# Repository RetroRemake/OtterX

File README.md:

# OtterX

An Open Source 6502-based, Commander X16-compatible, 8-bit Computer

## Where to buy?

Looking to order and build your own OtterX? Official kits are available from:

[Wavicle's store on Lectronz](https://lectronz.com/products/otterx-8-bit-retro-computer)

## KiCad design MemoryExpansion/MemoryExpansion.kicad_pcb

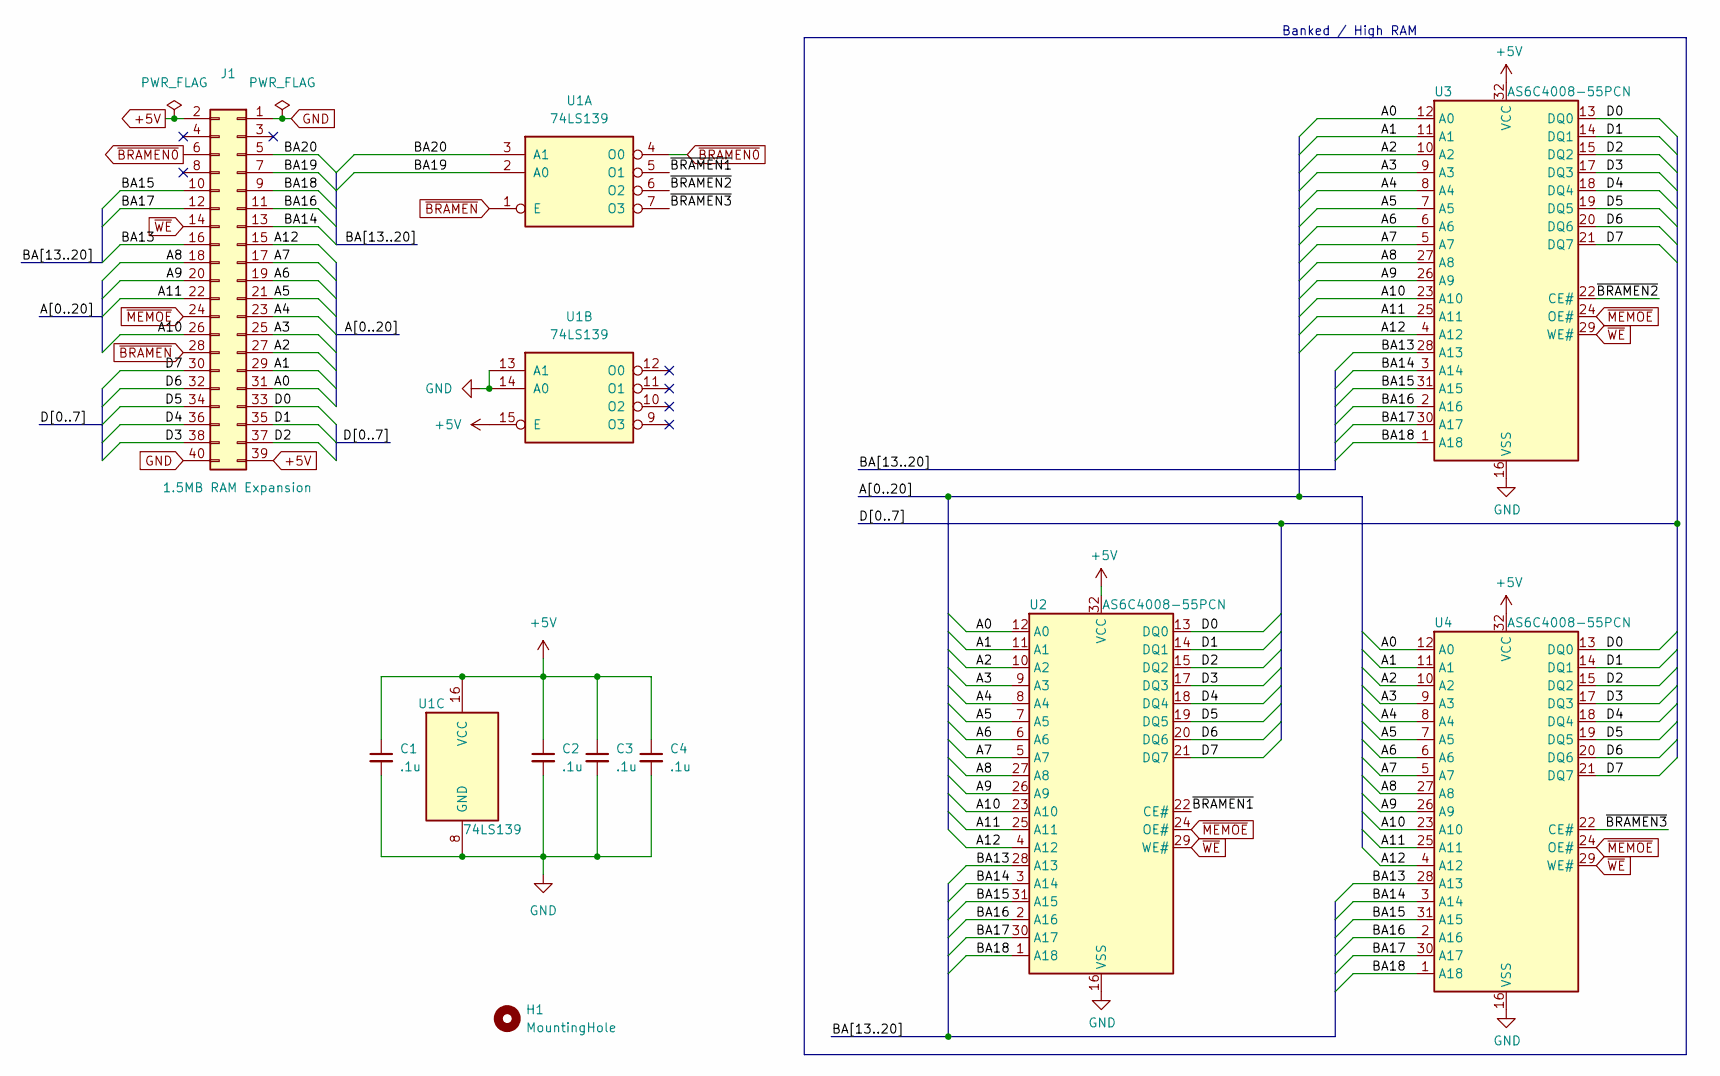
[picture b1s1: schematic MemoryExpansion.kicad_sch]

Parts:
C1, C2, C3, C4: .1u; C_Disc_D5.0mm_W2.5mm_P5.00mm
H1: MountingHole; MountingHole_2.2mm_M2
J1: 1.5MB RAM Expansion; PinHeader_2x20_P2.00mm_Vertical
U1: 74LS139; DIP-16_W7.62mm
U2, U3, U4: AS6C4008-55PCN; DIP-32_W15.24mm

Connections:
+5V: C1.1, C2.1, C3.1, C4.1, J1.2, J1.39, U1.15 (E), U1.16 (VCC), U2.32 (VCC), U3.32 (VCC), U4.32 (VCC)
/A0: J1.31, U2.12 (A0), U3.12 (A0), U4.12 (A0)
/A1: J1.29, U2.11 (A1), U3.11 (A1), U4.11 (A1)
/A2: J1.27, U2.10 (A2), U3.10 (A2), U4.10 (A2)
/A3: J1.25, U2.9 (A3), U3.9 (A3), U4.9 (A3)
/A4: J1.23, U2.8 (A4), U3.8 (A4), U4.8 (A4)
/A5: J1.21, U2.7 (A5), U3.7 (A5), U4.7 (A5)
/A6: J1.19, U2.6 (A6), U3.6 (A6), U4.6 (A6)
/A7: J1.17, U2.5 (A7), U3.5 (A7), U4.5 (A7)
/A8: J1.18, U2.27 (A8), U3.27 (A8), U4.27 (A8)
/A9: J1.20, U2.26 (A9), U3.26 (A9), U4.26 (A9)
/A10: J1.26, U2.23 (A10), U3.23 (A10), U4.23 (A10)
/A11: J1.22, U2.25 (A11), U3.25 (A11), U4.25 (A11)
/A12: J1.15, U2.4 (A12), U3.4 (A12), U4.4 (A12)
/BA13: J1.16, U2.28 (A13), U3.28 (A13), U4.28 (A13)
/BA14: J1.13, U2.3 (A14), U3.3 (A14), U4.3 (A14)
/BA15: J1.10, U2.31 (A15), U3.31 (A15), U4.31 (A15)
/BA16: J1.11, U2.2 (A16), U3.2 (A16), U4.2 (A16)
/BA17: J1.12, U2.30 (A17), U3.30 (A17), U4.30 (A17)
/BA18: J1.9, U2.1 (A18), U3.1 (A18), U4.1 (A18)
/BA19: J1.7, U1.2 (A0)
/BA20: J1.5, U1.3 (A1)
/D0: J1.33, U2.13 (DQ0), U3.13 (DQ0), U4.13 (DQ0)
/D1: J1.35, U2.14 (DQ1), U3.14 (DQ1), U4.14 (DQ1)
/D2: J1.37, U2.15 (DQ2), U3.15 (DQ2), U4.15 (DQ2)
/D3: J1.38, U2.17 (DQ3), U3.17 (DQ3), U4.17 (DQ3)
/D4: J1.36, U2.18 (DQ4), U3.18 (DQ4), U4.18 (DQ4)
/D5: J1.34, U2.19 (DQ5), U3.19 (DQ5), U4.19 (DQ5)
/D6: J1.32, U2.20 (DQ6), U3.20 (DQ6), U4.20 (DQ6)
/D7: J1.30, U2.21 (DQ7), U3.21 (DQ7), U4.21 (DQ7)
/~BRAMEN1: U1.5 (O1), U2.22 (CE#)
/~BRAMEN2: U1.6 (O2), U3.22 (CE#)
/~BRAMEN3: U1.7 (O3), U4.22 (CE#)
GND: C1.2, C2.2, C3.2, C4.2, J1.1, J1.40, U1.8 (GND), U1.13 (A1), U1.14 (A0), U2.16 (VSS), U3.16 (VSS), U4.16 (VSS)
~BRAMEN0: J1.6, U1.4 (O0)
~BRAMEN: J1.28, U1.1 (E)
~MEMOE: J1.24, U2.24 (OE#), U3.24 (OE#), U4.24 (OE#)
~WE: J1.14, U2.29 (WE#), U3.29 (WE#), U4.29 (WE#)

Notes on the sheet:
Banked / High RAM

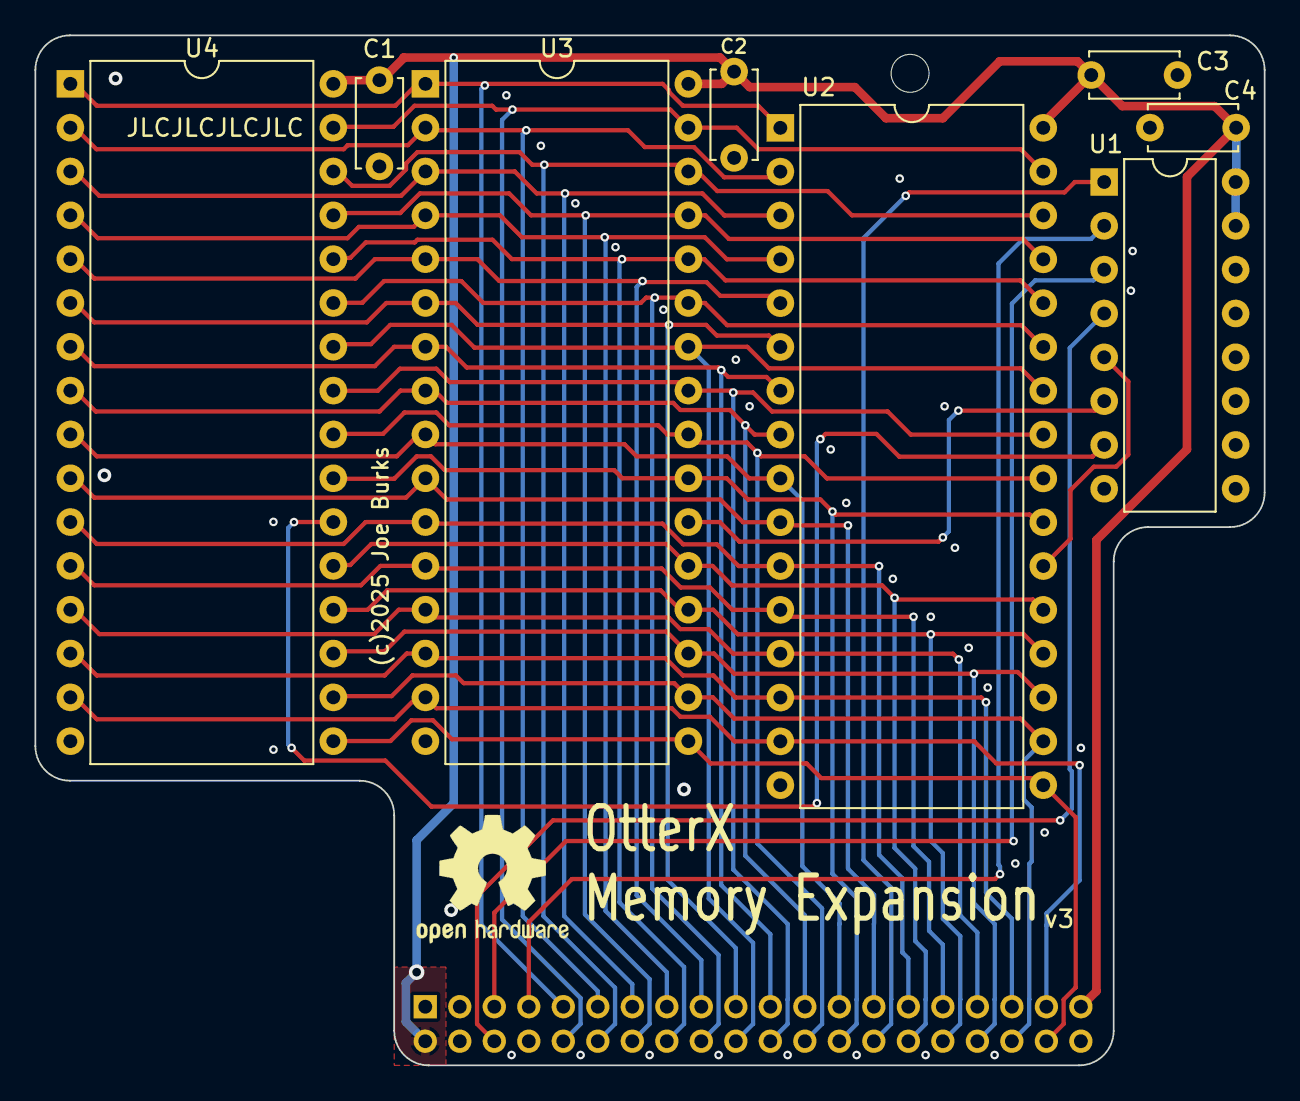
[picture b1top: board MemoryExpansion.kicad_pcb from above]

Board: 4 copper layers, 71.3 x 59.7 mm, 10 parts (1 on the bottom side), 38 nets.

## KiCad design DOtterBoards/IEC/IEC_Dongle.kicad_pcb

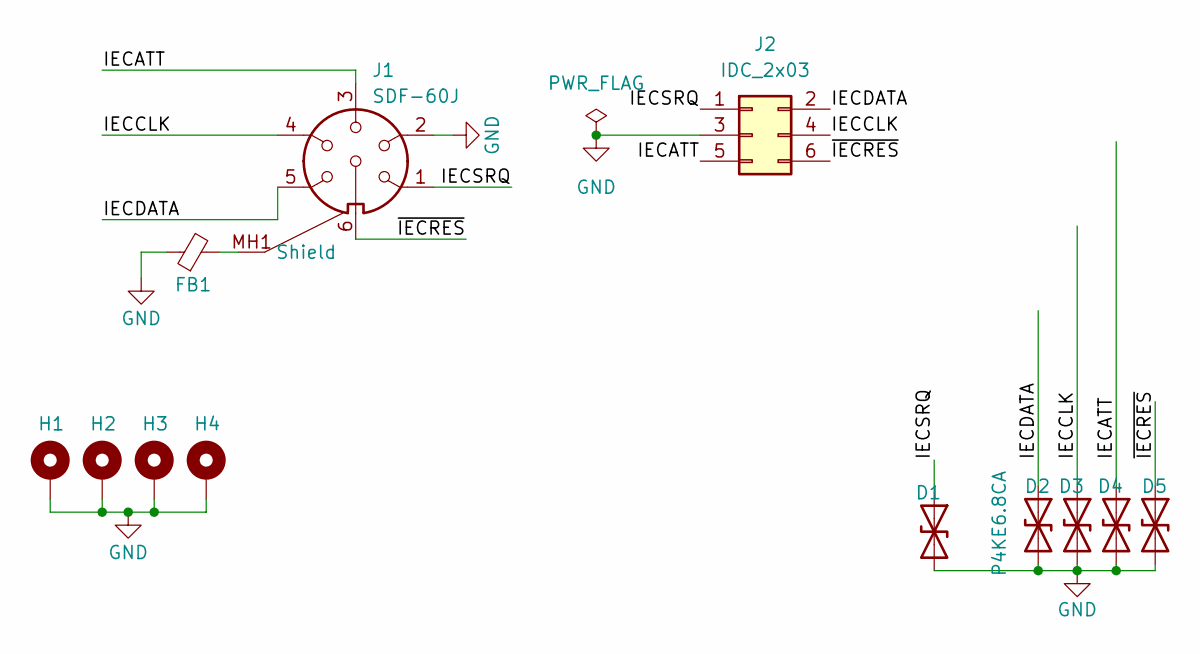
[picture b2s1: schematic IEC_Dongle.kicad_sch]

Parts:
D1, D2, D3, D4, D5: P4KE6.8CA; D_DO-41_SOD81_P7.62mm_Horizontal
FB1: FerriteBead_Small; L_Axial_L5.0mm_D3.6mm_P10.00mm_Horizontal_Murata_BL01RN1A2A2
H1, H2, H3, H4: MountingHole_Pad; MountingHole_2.7mm_M2.5_Pad_Via
J1: SDF-60J; SDF60J
J2: IDC_2x03; IDC-Header_2x03_P2.54mm_Vertical

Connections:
/IECATT: D4.1 (A1), J1.3, J2.5
/IECCLK: D3.1 (A1), J1.4, J2.4
/IECDATA: D2.1 (A1), J1.5, J2.2
/IECSRQ: D1.1 (A1), J1.1, J2.1
/~IECRES: D5.1 (A1), J1.6, J2.6
GND: D1.2 (A2), D2.2 (A2), D3.2 (A2), D4.2 (A2), D5.2 (A2), FB1.1, H1.1, H2.1, H3.1, H4.1, J1.2, J2.3
unnamed: FB1.2, J1.MH1 (Shield), J1.MH2

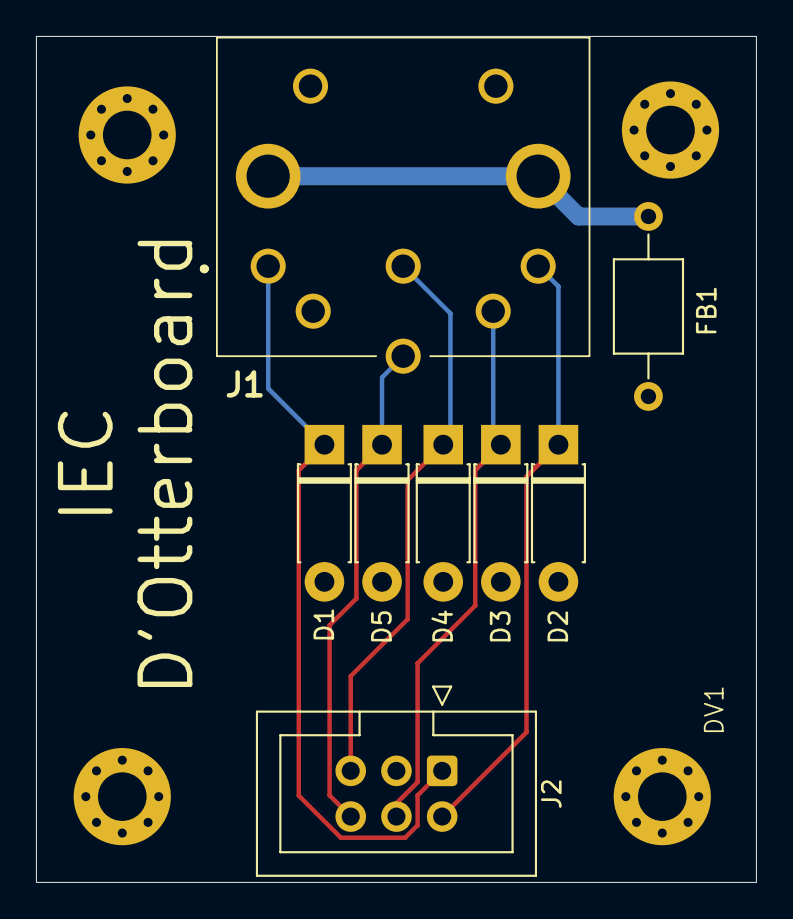
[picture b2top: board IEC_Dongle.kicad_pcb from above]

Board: 2 copper layers, 40.0 x 47.0 mm, 12 parts (0 on the bottom side), 7 nets.

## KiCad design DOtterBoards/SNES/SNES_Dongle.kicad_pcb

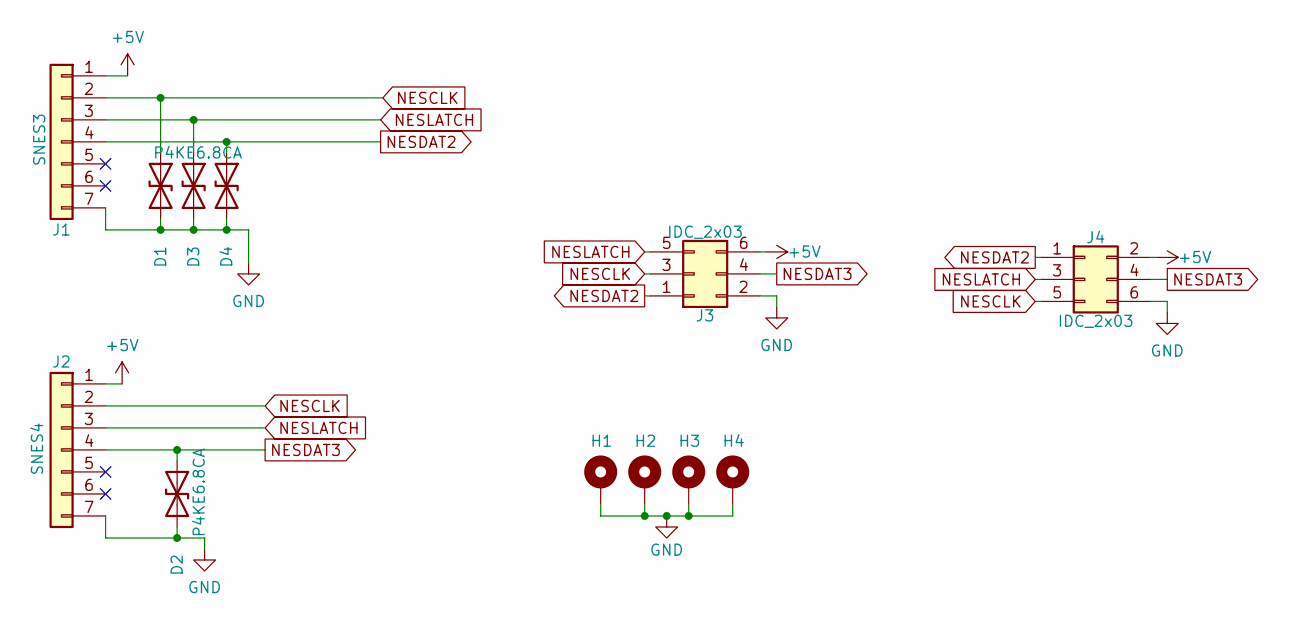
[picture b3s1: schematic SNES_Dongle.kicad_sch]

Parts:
D1, D2, D3, D4: P4KE6.8CA; D_DO-41_SOD81_P7.62mm_Horizontal
H1, H2, H3, H4: MountingHole_Pad; MountingHole_2.7mm_M2.5_Pad_Via
J1: SNES3; SNES_L
J2: SNES4; SNES_R
J3, J4: IDC_2x03; IDC-Header_2x03_P2.54mm_Vertical

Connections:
+5V: J1.1, J2.1, J3.6, J4.2
GND: D1.2 (A2), D2.2 (A2), D3.2 (A2), D4.2 (A2), H1.1, H2.1, H3.1, H4.1, J1.7, J2.7, J3.2, J4.6
NESCLK: D1.1 (A1), J1.2, J2.2, J3.3, J4.5
NESDAT2: D4.1 (A1), J1.4, J3.1, J4.1
NESDAT3: D2.1 (A1), J2.4, J3.4, J4.4
NESLATCH: D3.1 (A1), J1.3, J2.3, J3.5, J4.3

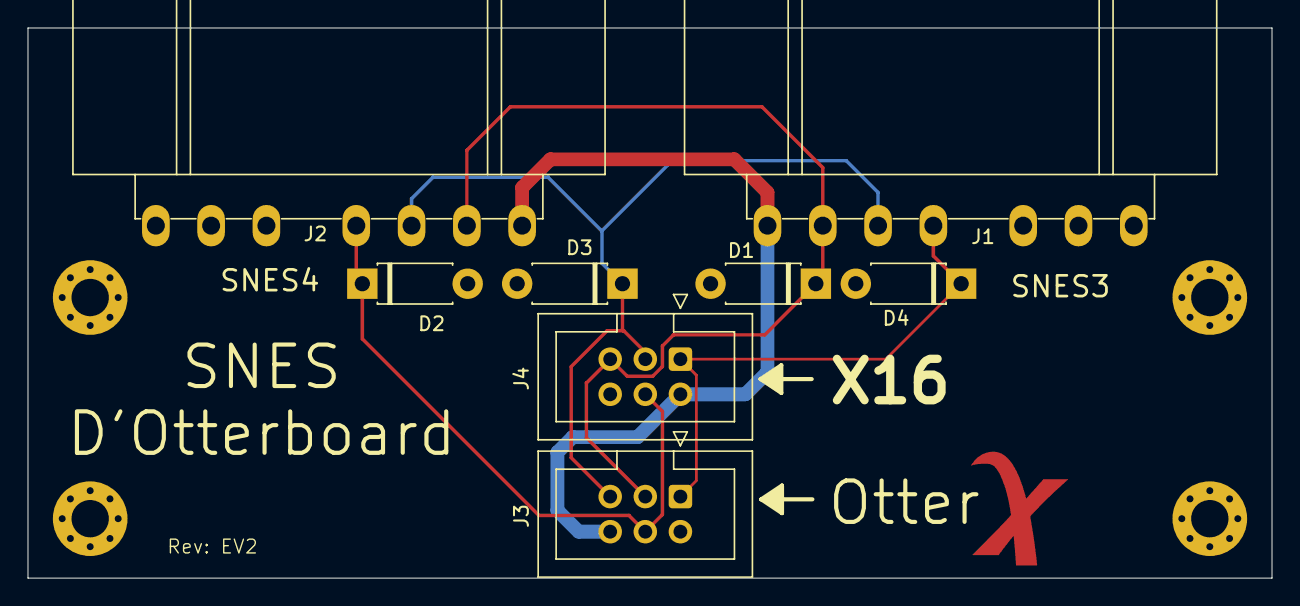
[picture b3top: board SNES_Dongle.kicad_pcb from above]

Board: 2 copper layers, 90.0 x 39.8 mm, 12 parts (0 on the bottom side), 6 nets.

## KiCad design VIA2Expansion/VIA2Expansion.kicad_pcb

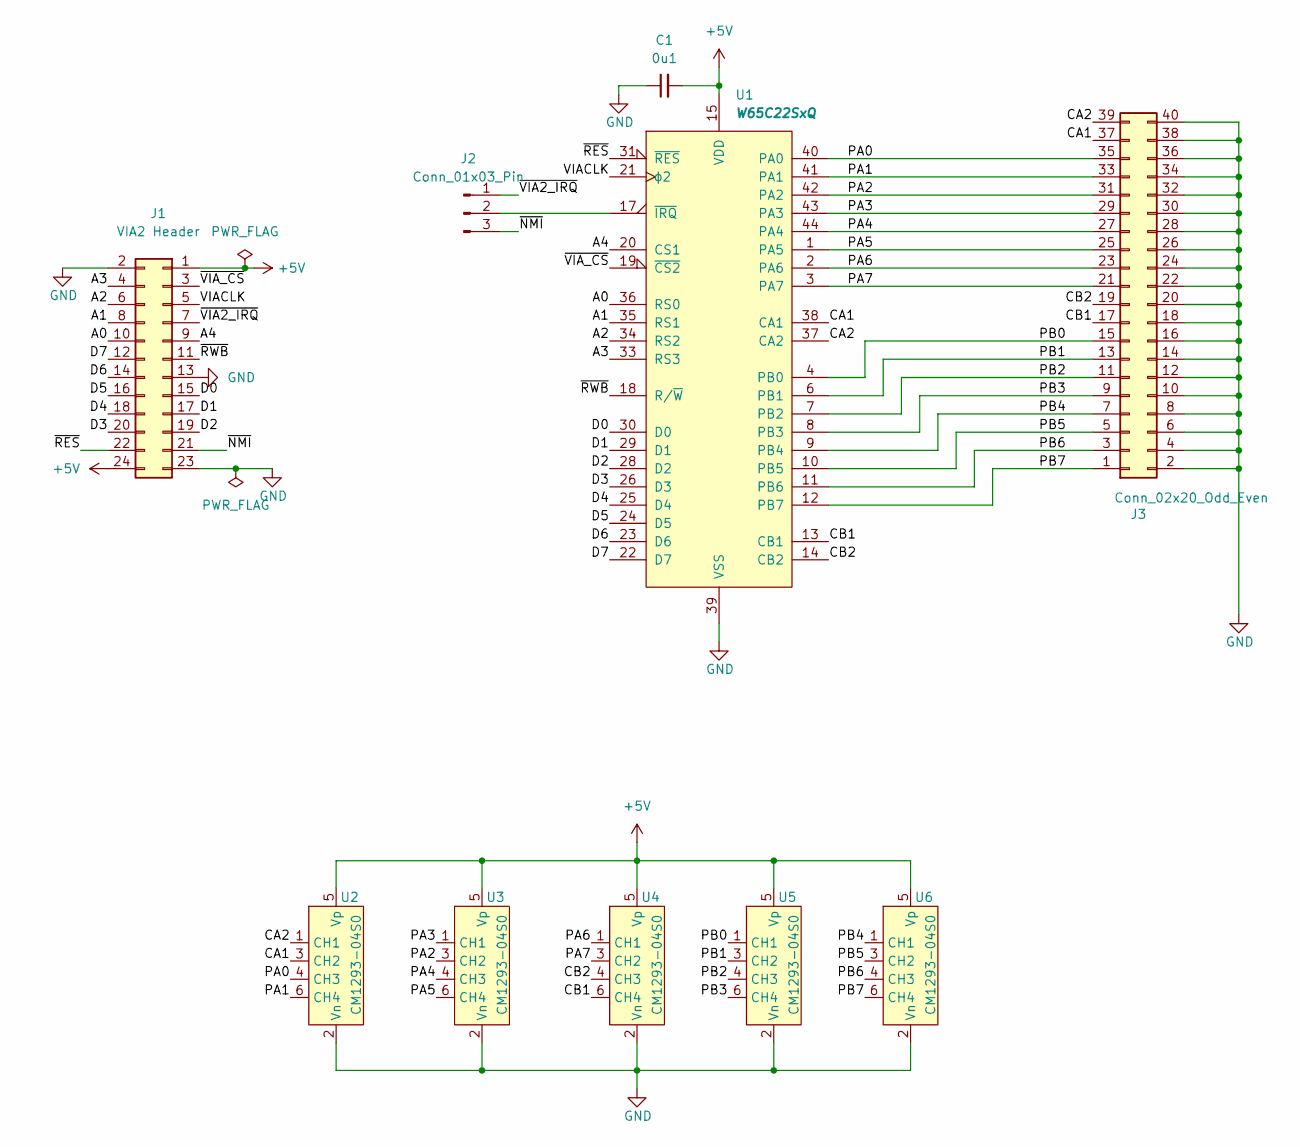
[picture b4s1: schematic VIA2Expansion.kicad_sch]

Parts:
C1: 0u1; C_0603_1608Metric
J1: VIA2 Header; PinSocket_2x12_P2.54mm_Horizontal
J2: Conn_01x03_Pin; PinHeader_1x03_P2.54mm_Vertical
J3: Conn_02x20_Odd_Even; IDC-Header_2x20_P2.54mm_Vertical
U1: W65C22SxQ; TQFP-44_10x10mm_P0.8mm
U2, U3, U4, U5, U6: CM1293-04S0; SC-74-6_1.55x2.9mm_P0.95mm

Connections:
+5V: C1.2, J1.1, J1.24, U1.15 (VDD), U2.5 (Vp), U3.5 (Vp), U4.5 (Vp), U5.5 (Vp), U6.5 (Vp)
/A0: J1.10, U1.36 (RS0)
/A1: J1.8, U1.35 (RS1)
/A2: J1.6, U1.34 (RS2)
/A3: J1.4, U1.33 (RS3)
/A4: J1.9, U1.20 (CS1)
/CA1: J3.37, U1.38 (CA1), U2.3 (CH2)
/CA2: J3.39, U1.37 (CA2), U2.1 (CH1)
/CB1: J3.17, U1.13 (CB1), U4.6 (CH4)
/CB2: J3.19, U1.14 (CB2), U4.4 (CH3)
/D0: J1.15, U1.30 (D0)
/D1: J1.17, U1.29 (D1)
/D2: J1.19, U1.28 (D2)
/D3: J1.20, U1.26 (D3)
/D4: J1.18, U1.25 (D4)
/D5: J1.16, U1.24 (D5)
/D6: J1.14, U1.23 (D6)
/D7: J1.12, U1.22 (D7)
/PA0: J3.35, U1.40 (PA0), U2.4 (CH3)
/PA1: J3.33, U1.41 (PA1), U2.6 (CH4)
/PA2: J3.31, U1.42 (PA2), U3.3 (CH2)
/PA3: J3.29, U1.43 (PA3), U3.1 (CH1)
/PA4: J3.27, U1.44 (PA4), U3.4 (CH3)
/PA5: J3.25, U1.1 (PA5), U3.6 (CH4)
/PA6: J3.23, U1.2 (PA6), U4.1 (CH1)
/PA7: J3.21, U1.3 (PA7), U4.3 (CH2)
/PB0: J3.15, U1.4 (PB0), U5.1 (CH1)
/PB1: J3.13, U1.6 (PB1), U5.3 (CH2)
/PB2: J3.11, U1.7 (PB2), U5.4 (CH3)
/PB3: J3.9, U1.8 (PB3), U5.6 (CH4)
/PB4: J3.7, U1.9 (PB4), U6.1 (CH1)
/PB5: J3.5, U1.10 (PB5), U6.3 (CH2)
/PB6: J3.3, U1.11 (PB6), U6.4 (CH3)
/PB7: J3.1, U1.12 (PB7), U6.6 (CH4)
/VIACLK: J1.5, U1.21 (ϕ2)
/~NMI: J1.21, J2.3
/~RES: J1.22, U1.31 (~RES)
/~RWB: J1.11, U1.18 (R/~W)
/~VIA2_IRQ: J1.7, J2.1
/~VIA_CS: J1.3, U1.19 (~CS2)
GND: C1.1, J1.2, J1.13, J1.23, J3.2, J3.4, J3.6, J3.8, J3.10, J3.12, J3.14, J3.16, J3.18, J3.20, J3.22, J3.24, J3.26, J3.28, J3.30, J3.32, J3.34, J3.36, J3.38, J3.40, U1.39 (VSS), U2.2 (Vn), U3.2 (Vn), U4.2 (Vn), U5.2 (Vn), U6.2 (Vn)
unnamed: J2.2, U1.17 (~IRQ)

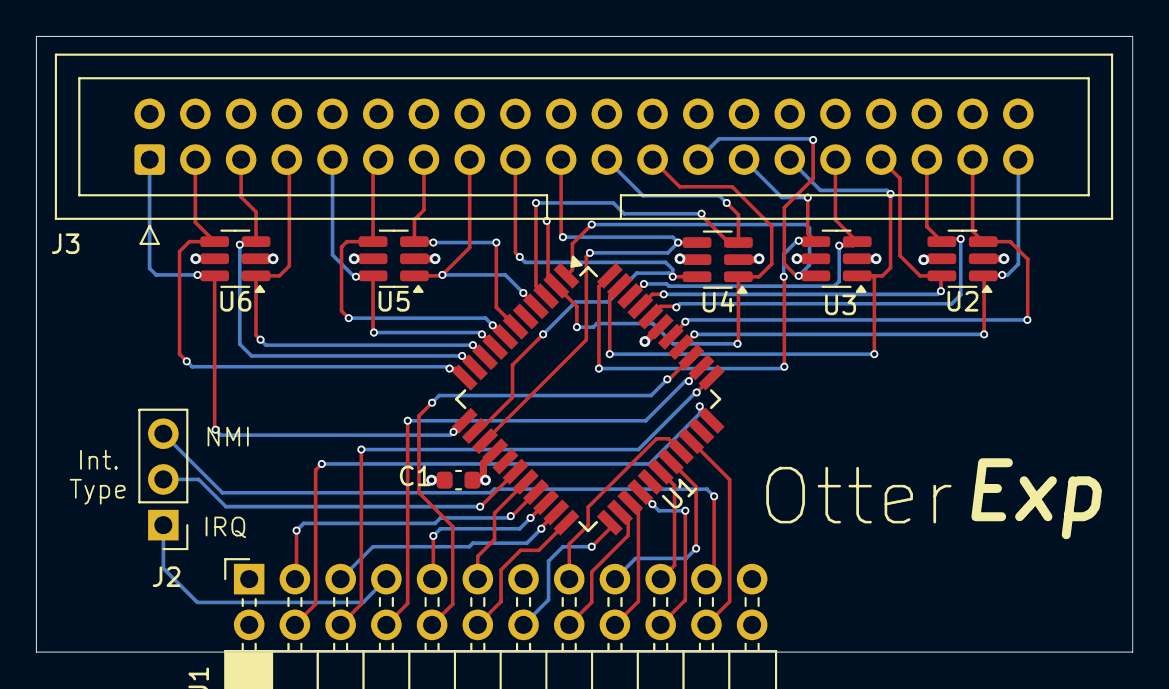
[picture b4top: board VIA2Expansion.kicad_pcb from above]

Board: 4 copper layers, 60.9 x 34.2 mm, 10 parts (0 on the bottom side), 42 nets.

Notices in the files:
MemoryExpansion/MemoryExpansion.kicad_pcb:
(c)2025 Joe Burks
